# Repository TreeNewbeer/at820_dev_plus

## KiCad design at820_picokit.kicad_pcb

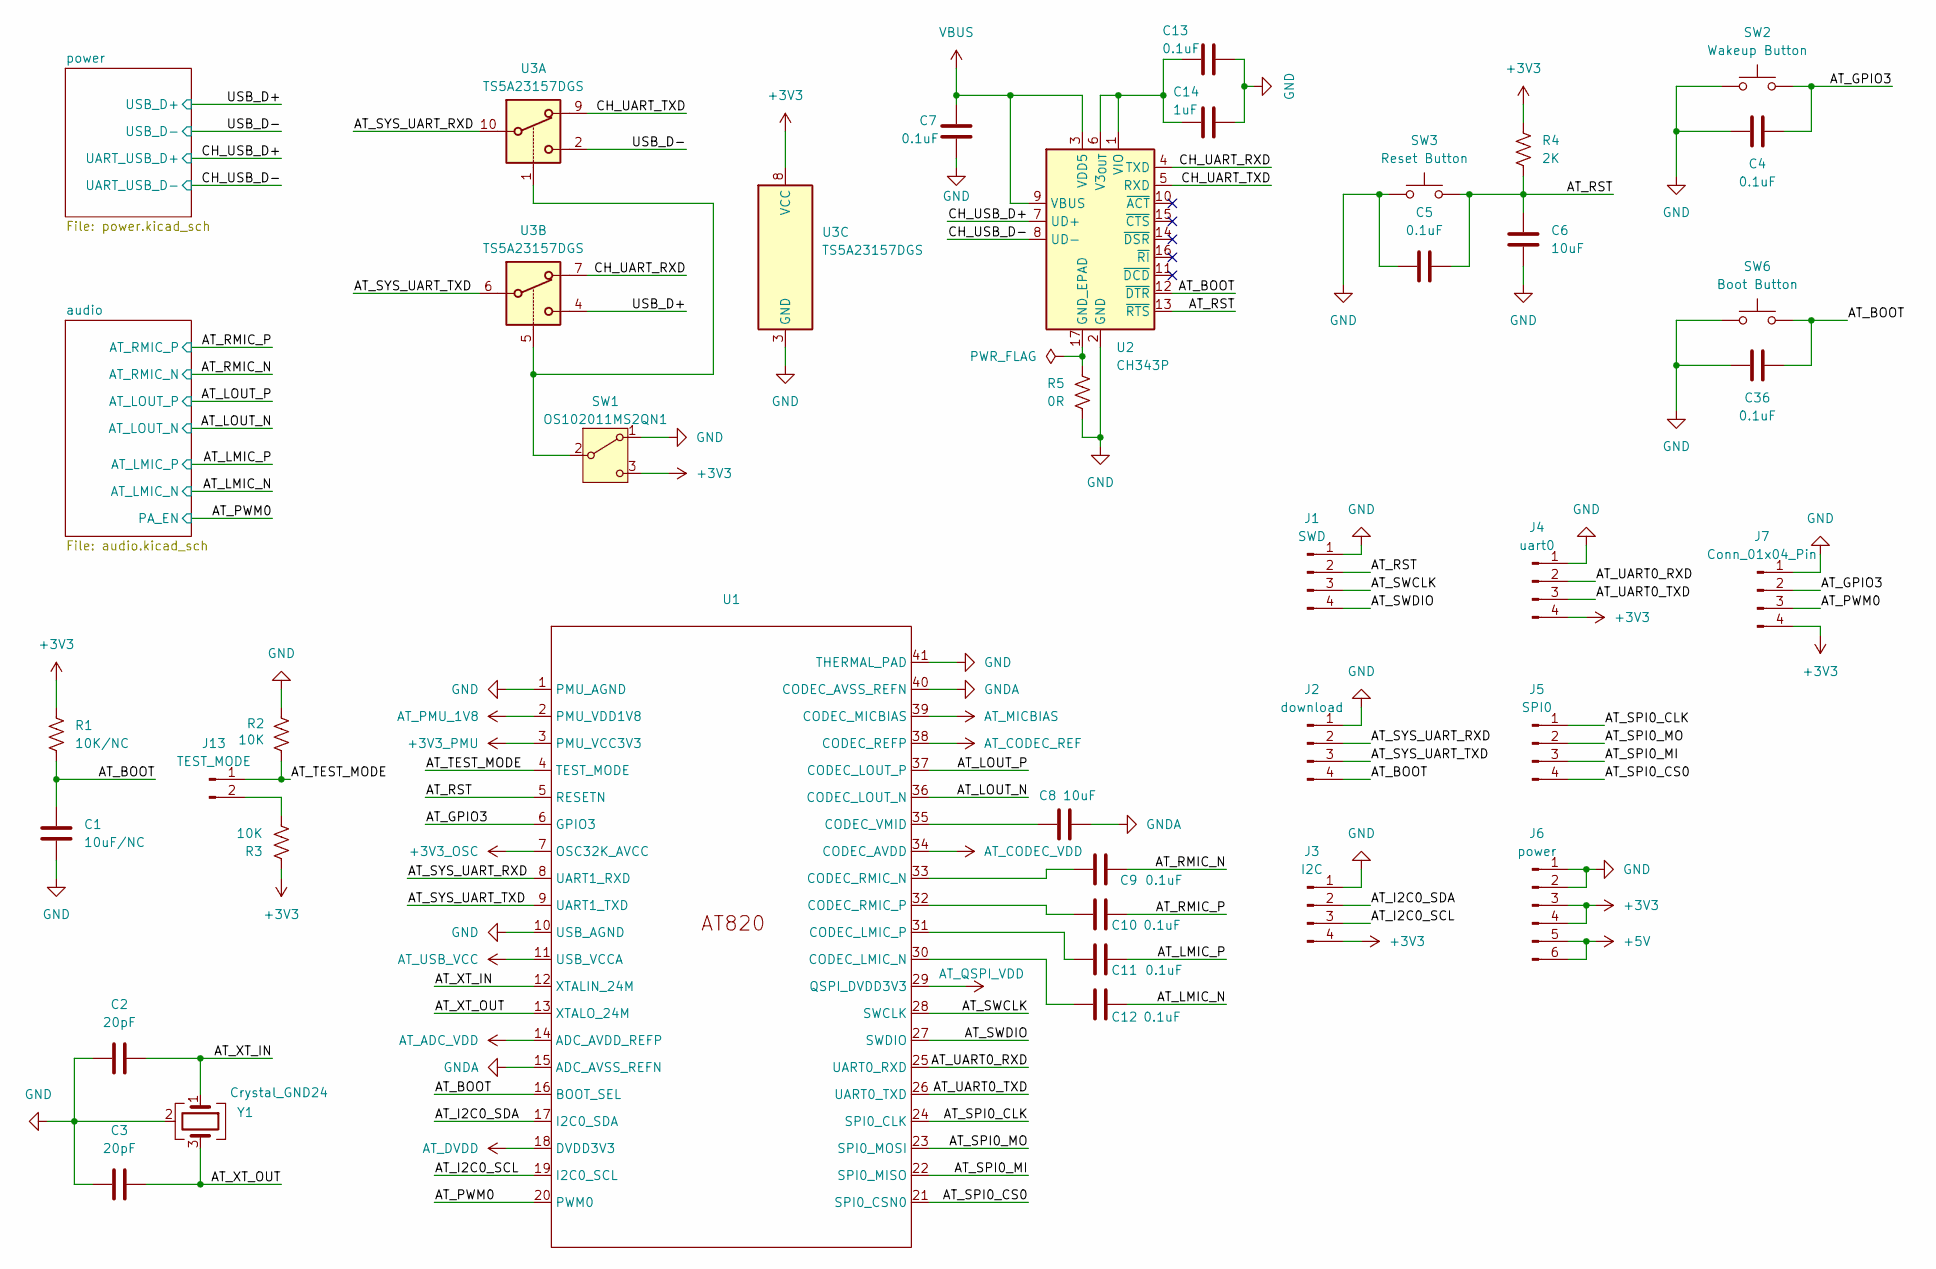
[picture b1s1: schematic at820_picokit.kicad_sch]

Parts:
C1: 10uF/NC; C_0603_1608Metric_Pad1.08x0.95mm_HandSolder
C2, C3: 20pF; C_0603_1608Metric_Pad1.08x0.95mm_HandSolder
C4, C5, C7, C9, C10, C11, C12, C13, C36: 0.1uF; C_0603_1608Metric_Pad1.08x0.95mm_HandSolder
C6, C8: 10uF; C_0603_1608Metric_Pad1.08x0.95mm_HandSolder
C14: 1uF; C_0603_1608Metric_Pad1.08x0.95mm_HandSolder
J1: SWD; PinHeader_1x04_P2.54mm_Vertical
J2: download; PinHeader_1x04_P2.54mm_Vertical
J3: I2C; PinHeader_1x04_P2.54mm_Vertical
J4: uart0; PinHeader_1x04_P2.54mm_Vertical
J5: SPI0; PinHeader_1x04_P2.54mm_Vertical
J6: power; PinHeader_1x06_P2.54mm_Vertical
J7: Conn_01x04_Pin; PinHeader_1x04_P2.54mm_Vertical
J13: TEST_MODE; PinHeader_1x02_P2.54mm_Vertical
R1: 10K/NC; R_0603_1608Metric_Pad0.98x0.95mm_HandSolder
R2, R3: 10K; R_0603_1608Metric_Pad0.98x0.95mm_HandSolder
R4: 2K; R_0603_1608Metric_Pad0.98x0.95mm_HandSolder
R5: 0R; R_0603_1608Metric_Pad0.98x0.95mm_HandSolder
SW1: OS102011MS2QN1; SW_Slide_SPDT_Straight_CK_OS102011MS2Q
SW2: Wakeup Button; SW_SPST_PTS810
SW3: Reset Button; SW_SPST_PTS810
SW6: Boot Button; SW_SPST_PTS810
U1: QFN-40-1EP_5x5mm_P0.4mm_EP3.6x3.6mm
U2: CH343P; WCH_QFN-16-1EP_3x3mm_P0.5mm_EP1.8x1.8mm
U3: TS5A23157DGS; TSSOP-10_3x3mm_P0.5mm
Y1: Crystal_GND24; Crystal_SMD_3225-4Pin_3.2x2.5mm_HandSoldering

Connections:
+3V3: J3.4, J4.4, J6.3, J6.4, J7.4, R1.1, R3.1, R4.1, SW1.3 (C), U1.3 (PMU_VCC3V3), U1.7 (OSC32K_AVCC), U1.11 (USB_VCCA), U1.14 (ADC_AVDD_REFP), U1.18 (DVDD3V3), U1.34 (CODEC_AVDD), U3.8 (VCC); also elsewhere on the board
+5V: J6.5, J6.6; also elsewhere on the board
/AT_BOOT: C1.1, C36.2, J2.4, R1.2, SW6.2, U1.16 (BOOT_SEL), U2.12 (~DTR)
/AT_GPIO3: C4.2, J7.2, SW2.2, U1.6 (GPIO3)
/AT_I2C0_SCL: J3.3, U1.19 (I2C0_SCL)
/AT_I2C0_SDA: J3.2, U1.17 (I2C0_SDA)
/AT_LMIC_N: C12.1; also elsewhere on the board
/AT_LMIC_P: C11.1; also elsewhere on the board
/AT_LOUT_N: U1.36 (CODEC_LOUT_N); also elsewhere on the board
/AT_LOUT_P: U1.37 (CODEC_LOUT_P); also elsewhere on the board
/AT_PWM0: J7.3, U1.20 (PWM0); also elsewhere on the board
/AT_RMIC_N: C9.1; also elsewhere on the board
/AT_RMIC_P: C10.1; also elsewhere on the board
/AT_RST: C5.2, C6.1, J1.2, R4.2, SW3.2, U1.5 (RESETN), U2.13 (~RTS)
/AT_SPI0_CLK: J5.1, U1.24 (SPI0_CLK)
/AT_SPI0_CS0: J5.4, U1.21 (SPI0_CSN0)
/AT_SPI0_MI: J5.3, U1.22 (SPI0_MISO)
/AT_SPI0_MO: J5.2, U1.23 (SPI0_MOSI)
/AT_SWCLK: J1.3, U1.28 (SWCLK)
/AT_SWDIO: J1.4, U1.27 (SWDIO)
/AT_SYS_UART_RXD: J2.2, U1.8 (UART1_RXD), U3.10
/AT_SYS_UART_TXD: J2.3, U1.9 (UART1_TXD), U3.6
/AT_TEST_MODE: J13.1, R2.1, U1.4 (TEST_MODE)
/AT_UART0_RXD: J4.2, U1.25 (UART0_RXD)
/AT_UART0_TXD: J4.3, U1.26 (UART0_TXD)
/AT_XT_IN: C2.1, U1.12 (XTALIN_24M), Y1.1
/AT_XT_OUT: C3.1, U1.13 (XTALO_24M), Y1.3
/CH_UART_RXD: U2.4 (TXD), U3.7
/CH_UART_TXD: U2.5 (RXD), U3.9
/CH_USB_D+: U2.7 (UD+); also elsewhere on the board
/CH_USB_D-: U2.8 (UD-); also elsewhere on the board
/USB_D+: U3.4; also elsewhere on the board
/USB_D-: U3.2; also elsewhere on the board
AT_CODEC_REF: U1.38 (CODEC_REFP); also elsewhere on the board
AT_MICBIAS: U1.39 (CODEC_MICBIAS); also elsewhere on the board
AT_PMU_1V8: U1.2 (PMU_VDD1V8); also elsewhere on the board
AT_QSPI_VDD: U1.29 (QSPI_DVDD3V3); also elsewhere on the board
GND: C1.2, C2.2, C3.2, C4.1, C5.1, C6.2, C7.2, C13.2, C14.2, C36.1, J1.1, J2.1, J3.1, J4.1, J6.1, J6.2, J7.1, R2.2, R5.1, SW1.1 (A), SW2.1, SW3.1, SW6.1, U1.1 (PMU_AGND), U1.10 (USB_AGND), U1.41 (THERMAL_PAD), U2.2 (GND), U3.3 (GND), Y1.2 (G), Y1.4 (G); also elsewhere on the board
GNDA: C8.1, U1.15 (ADC_AVSS_REFN), U1.40 (CODEC_AVSS_REFN); also elsewhere on the board
unnamed: J13.2, R3.2
unnamed: SW1.2 (B), U3.1, U3.5
unnamed: C12.2, U1.30 (CODEC_LMIC_N)
unnamed: C11.2, U1.31 (CODEC_LMIC_P)
unnamed: C9.2, U1.33 (CODEC_RMIC_N)
unnamed: C10.2, U1.32 (CODEC_RMIC_P)
unnamed: C8.2, U1.35 (CODEC_VMID)
unnamed: R5.2, U2.17 (GND_EPAD)
unnamed: C13.1, C14.1, U2.1 (VIO), U2.6 (V3_{OUT})
VBUS: C7.1, U2.3 (VDD5), U2.9 (VBUS); also elsewhere on the board

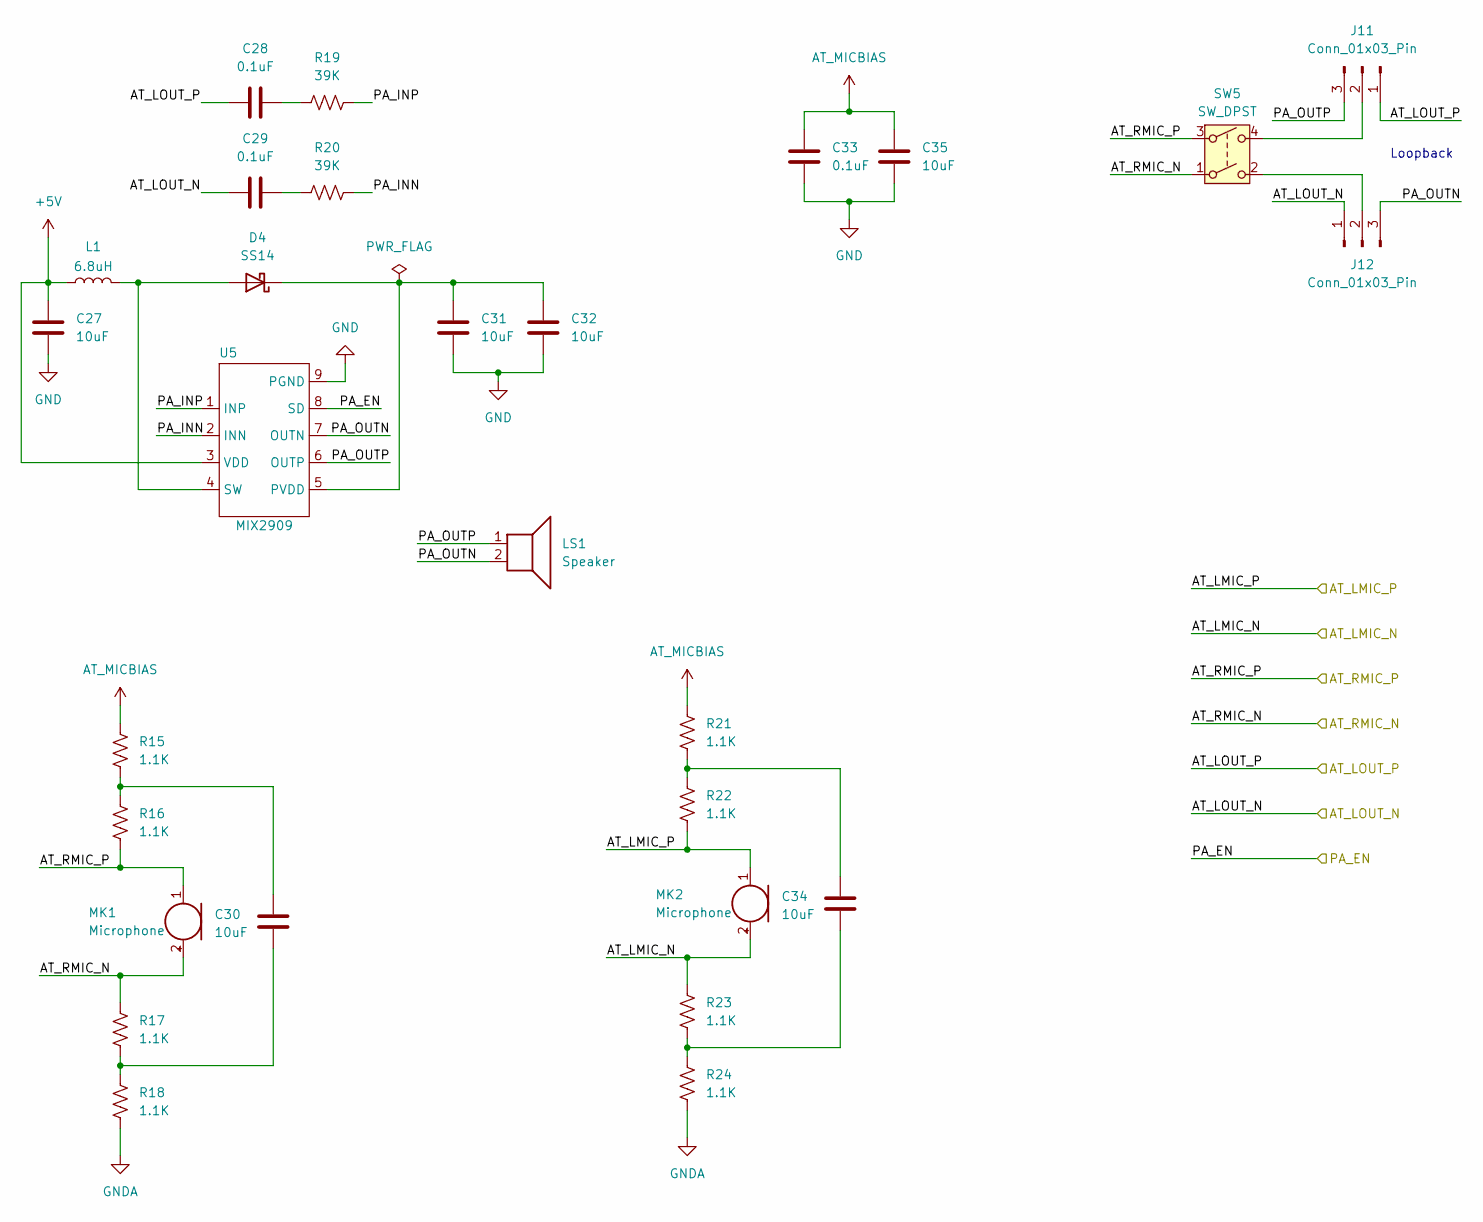
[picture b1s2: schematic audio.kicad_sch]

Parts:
C27, C30, C31, C32, C34, C35: 10uF; C_0603_1608Metric_Pad1.08x0.95mm_HandSolder
C28, C29, C33: 0.1uF; C_0603_1608Metric_Pad1.08x0.95mm_HandSolder
D4: SS14; D_SMA-SMB_Universal_Handsoldering
J11, J12: Conn_01x03_Pin; PinHeader_1x03_P2.54mm_Vertical
L1: 6.8uH; L_Sunlord_MWSA0402S
LS1: Speaker; Molex_PicoBlade_53047-0210_1x02_P1.25mm_Vertical
MK1, MK2: Microphone; CP_Radial_D4.0mm_P1.50mm
R15, R16, R17, R18, R21, R22, R23, R24: 1.1K; R_0603_1608Metric_Pad0.98x0.95mm_HandSolder
R19, R20: 39K; R_0603_1608Metric_Pad0.98x0.95mm_HandSolder
SW5: SW_DPST; SW_DIP_SPSTx02_Slide_Copal_CHS-02B_W7.62mm_P1.27mm
U5: MIX2909; SOIC-8-1EP_3.9x4.9mm_P1.27mm_EP2.29x3mm_ThermalVias

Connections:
+5V: C27.1, L1.1, U5.3 (VDD); also elsewhere on the board
/AT_LMIC_N: MK2.2 (+), R23.1; also elsewhere on the board
/AT_LMIC_P: MK2.1 (-), R22.2; also elsewhere on the board
/AT_LOUT_N: C29.1, J12.1; also elsewhere on the board
/AT_LOUT_P: C28.1, J11.1; also elsewhere on the board
/AT_PWM0: U5.8 (SD); also elsewhere on the board
/AT_RMIC_N: MK1.2 (+), R17.1, SW5.1; also elsewhere on the board
/AT_RMIC_P: MK1.1 (-), R16.2, SW5.3; also elsewhere on the board
/audio/PA_INN: R20.2, U5.2 (INN)
/audio/PA_INP: R19.2, U5.1 (INP)
/audio/PA_OUTN: J12.3, LS1.2, U5.7 (OUTN)
/audio/PA_OUTP: J11.3, LS1.1, U5.6 (OUTP)
AT_MICBIAS: C33.1, C35.1, R15.1, R21.1; also elsewhere on the board
GND: C27.2, C31.2, C32.2, C33.2, C35.2, U5.9 (PGND); also elsewhere on the board
GNDA: R18.2, R24.2; also elsewhere on the board
unnamed: C28.2, R19.1
unnamed: C29.2, R20.1
unnamed: C30.1, R17.2, R18.1
unnamed: C30.2, R15.2, R16.1
unnamed: C34.1, R23.2, R24.1
unnamed: C34.2, R21.2, R22.1
unnamed: D4.2 (A), L1.2, U5.4 (SW)
unnamed: C31.1, C32.1, D4.1 (K), U5.5 (PVDD)
unnamed: J11.2, SW5.4
unnamed: J12.2, SW5.2

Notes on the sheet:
Loopback

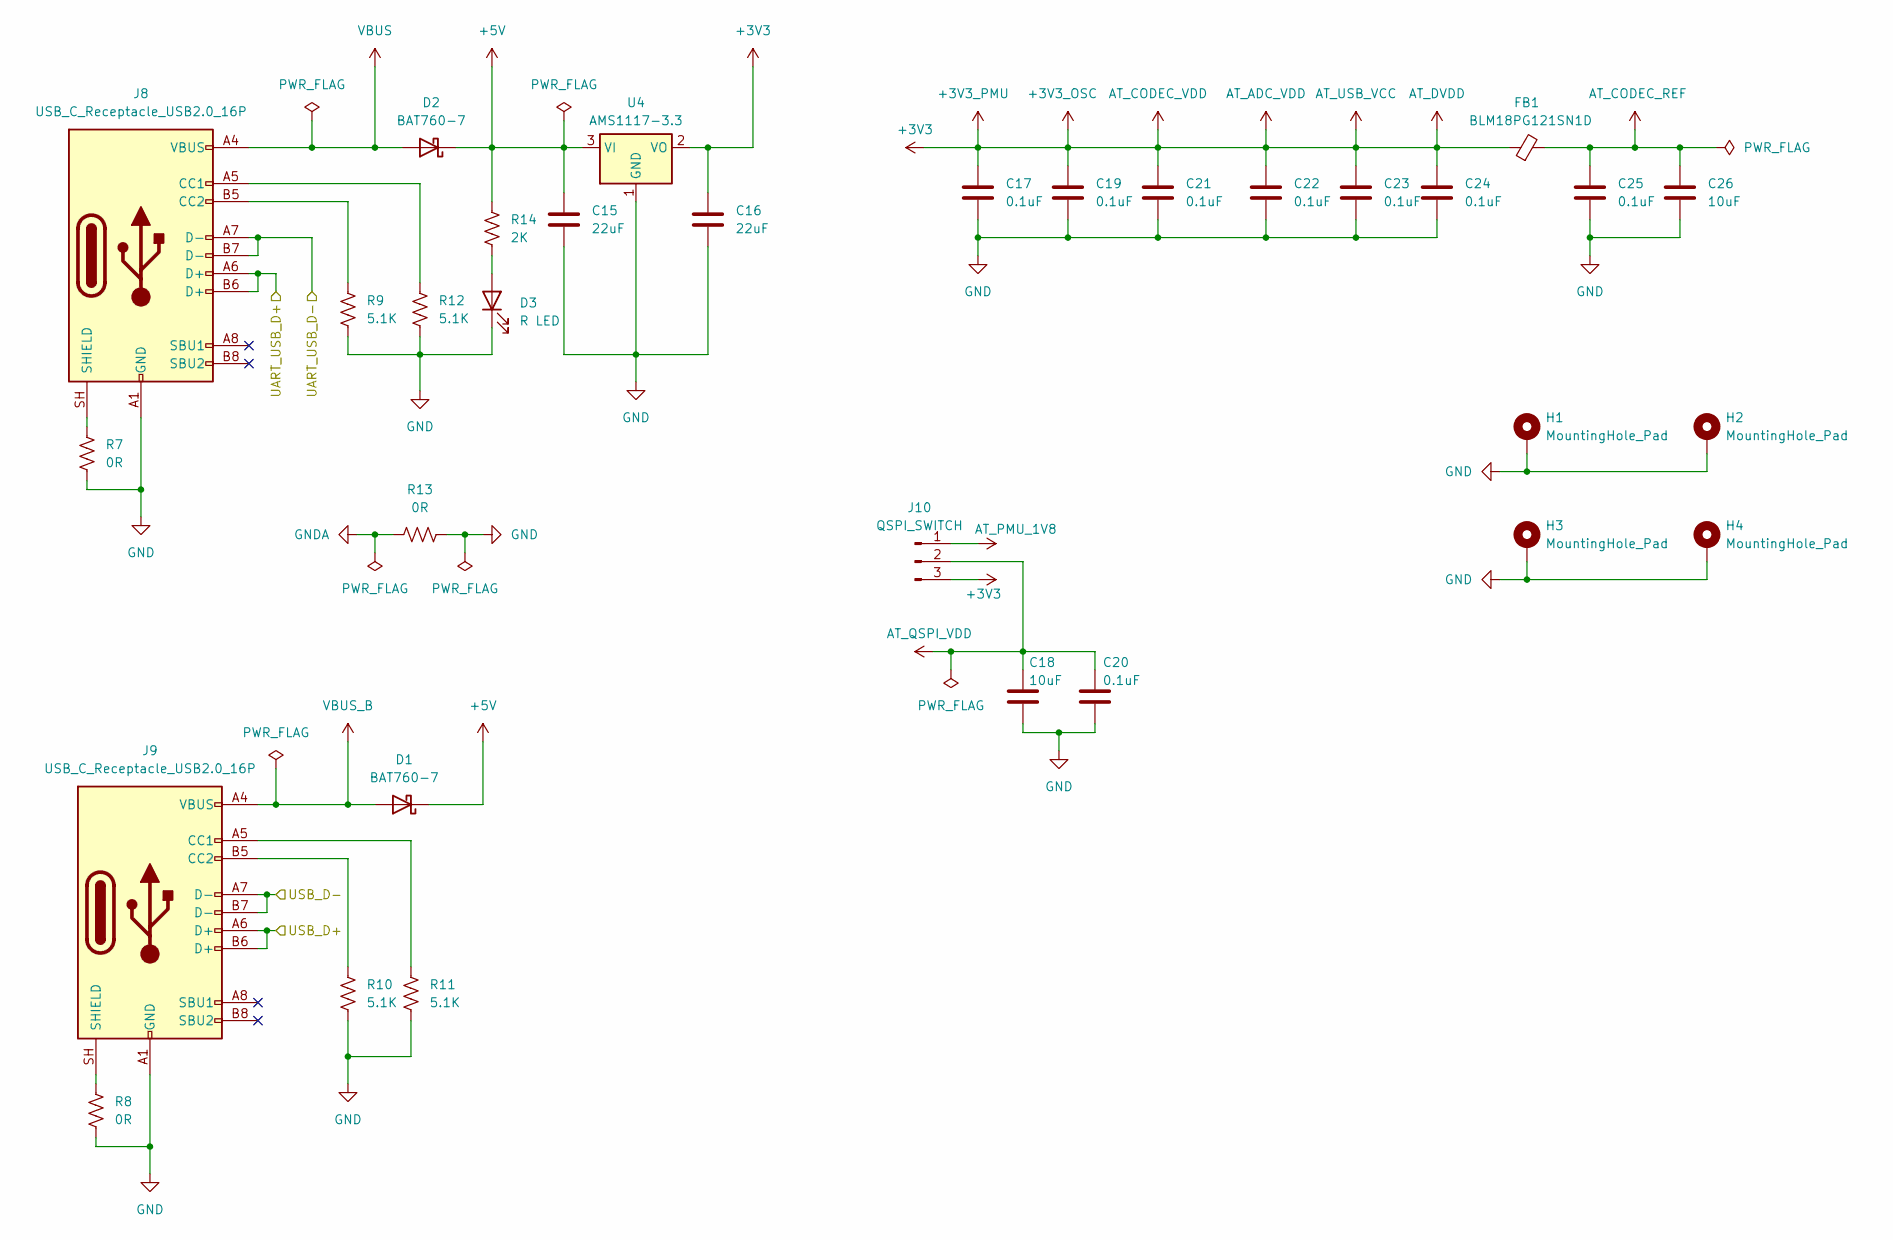
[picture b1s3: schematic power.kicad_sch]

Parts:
C15, C16: 22uF; C_0603_1608Metric_Pad1.08x0.95mm_HandSolder
C17, C19, C20, C21, C22, C23, C24, C25: 0.1uF; C_0603_1608Metric_Pad1.08x0.95mm_HandSolder
C18, C26: 10uF; C_0603_1608Metric_Pad1.08x0.95mm_HandSolder
D1, D2: BAT760-7; D_SOD-323_HandSoldering
D3: R LED; LED_0603_1608Metric_Pad1.05x0.95mm_HandSolder
FB1: BLM18PG121SN1D; L_0603_1608Metric_Pad1.05x0.95mm_HandSolder
H1, H2, H3, H4: MountingHole_Pad; MountingHole_3.2mm_M3_Pad
J8, J9: USB_C_Receptacle_USB2.0_16P; USB_C_Receptacle_GCT_USB4105-xx-A_16P_TopMnt_Horizontal
J10: QSPI_SWITCH; PinHeader_1x03_P2.54mm_Vertical
R7, R8, R13: 0R; R_0603_1608Metric_Pad0.98x0.95mm_HandSolder
R9, R10, R11, R12: 5.1K; R_0603_1608Metric_Pad0.98x0.95mm_HandSolder
R14: 2K; R_0603_1608Metric_Pad0.98x0.95mm_HandSolder
U4: AMS1117-3.3; SOT-223-3_TabPin2

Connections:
+3V3: C16.1, C17.1, C19.1, C21.1, C22.1, C23.1, C24.1, FB1.1, J10.3, U4.2 (VO); also elsewhere on the board
+5V: C15.1, D1.1 (K), D2.1 (K), R14.1, U4.3 (VI); also elsewhere on the board
/CH_USB_D+: J8.A6 (D+), J8.B6 (D+); also elsewhere on the board
/CH_USB_D-: J8.A7 (D-), J8.B7 (D-); also elsewhere on the board
/USB_D+: J9.A6 (D+), J9.B6 (D+); also elsewhere on the board
/USB_D-: J9.A7 (D-), J9.B7 (D-); also elsewhere on the board
AT_CODEC_REF: C25.1, C26.1, FB1.2; also elsewhere on the board
AT_PMU_1V8: J10.1; also elsewhere on the board
AT_QSPI_VDD: C18.1, C20.1, J10.2; also elsewhere on the board
GND: C15.2, C16.2, C17.2, C18.2, C19.2, C20.2, C21.2, C22.2, C23.2, C24.2, C25.2, C26.2, D3.1 (K), H1.1 (1_1), H2.1 (1_1), H3.1 (1_1), H4.1 (1_1), J8.A1 (GND), J8.A12 (GND), J8.B1 (GND), J8.B12 (GND), J9.A1 (GND), J9.A12 (GND), J9.B1 (GND), J9.B12 (GND), R7.1, R8.1, R9.2, R10.2, R11.2, R12.2, R13.2, U4.1 (GND); also elsewhere on the board
GNDA: R13.1; also elsewhere on the board
unnamed: D3.2 (A), R14.2
unnamed: J8.A5 (CC1), R12.1
unnamed: J8.B5 (CC2), R9.1
unnamed: J8.SH (SHIELD), R7.2
unnamed: J9.A5 (CC1), R11.1
unnamed: J9.B5 (CC2), R10.1
unnamed: J9.SH (SHIELD), R8.2
VBUS: D2.2 (A), J8.A4 (VBUS), J8.A9 (VBUS), J8.B4 (VBUS), J8.B9 (VBUS); also elsewhere on the board
VBUS_B: D1.2 (A), J9.A4 (VBUS), J9.A9 (VBUS), J9.B4 (VBUS), J9.B9 (VBUS)

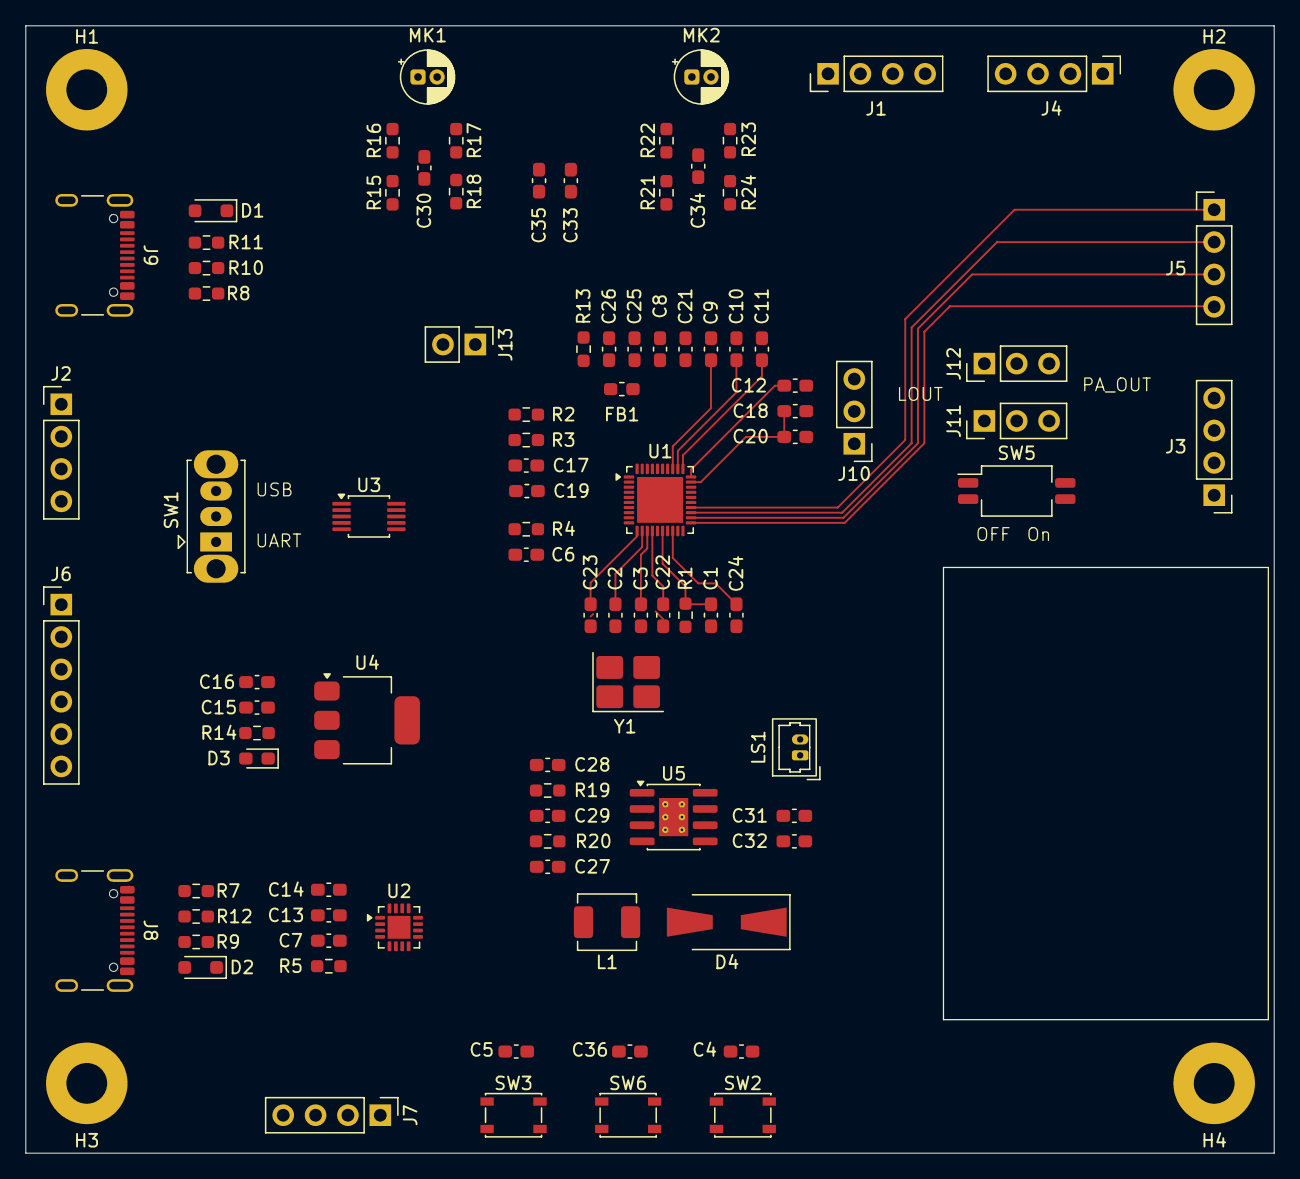
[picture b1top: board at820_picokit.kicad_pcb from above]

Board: 2 copper layers, 98.0 x 88.5 mm, 96 parts (0 on the bottom side), 71 nets.

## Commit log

2026-04-23 init repo
2026-04-24 fix at820 sym, impl audio pa
2026-04-25 sch features done, all drc passed
2026-04-26 asigning footprint
2026-04-28 refactor some switch circuit
2026-05-01 sch all done, footprint done
2026-05-01 components loc done, pcb ing
